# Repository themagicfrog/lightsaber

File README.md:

# MAGIC FROG'S LIGHTSABER

This is a PCB lightsaber controlled by a gyroscope and accelerometer that I designed. I created it originally for [The Trail](https://github.com/hackclub/the-trail), an event organized by [Hack Club](https://github.com/hackclub). 

## Project Overview
I initially designed the entire board with a ATmeag32U4 chip, and you can find the schematic and PCB design in the main branch. I also added some lighthouse-themed silkscreens as my original idea was to make it a desk lamp. I encountered a lot of problems along way and decided to use an Ardunio Nano instead. I used my PCB board as a base and connected the Ardunio Nano. 

## Features
Dynamic LED Control: LEDs light up based on movement detected by the gyroscope and acceleromenter.
- The faster you accelerate, the more LEDs illuminate.
- Each axis (x, y, z) on the gyroscope control a different LED color: red, blue, or green.

## Components
- Ardunio Nano Microcontroller
- MPU-6050 Gyroscope and Accelerometer
- NeoPixel LED Strip
- 6V Battery

## Photos!!
Here are some really cool long-exposure light photos I took with the lightsaber in action!

## Video
[Demo](https://youtu.be/aVmNQV3bQB4)

## Acknowledgements
Special thanks to [Thomas Stubblefield](https://github.com/serenityUX), Kevin Yang, and [Isaac Davenport](https://isaacdavenport.com/) for helping and encouraging me on the way!

## License
Magic Frog's Lightsaber is licensed under the MIT License. See the full license text in [License](https://github.com/themagicfrog/lightsaber/blob/main/LICENSE).

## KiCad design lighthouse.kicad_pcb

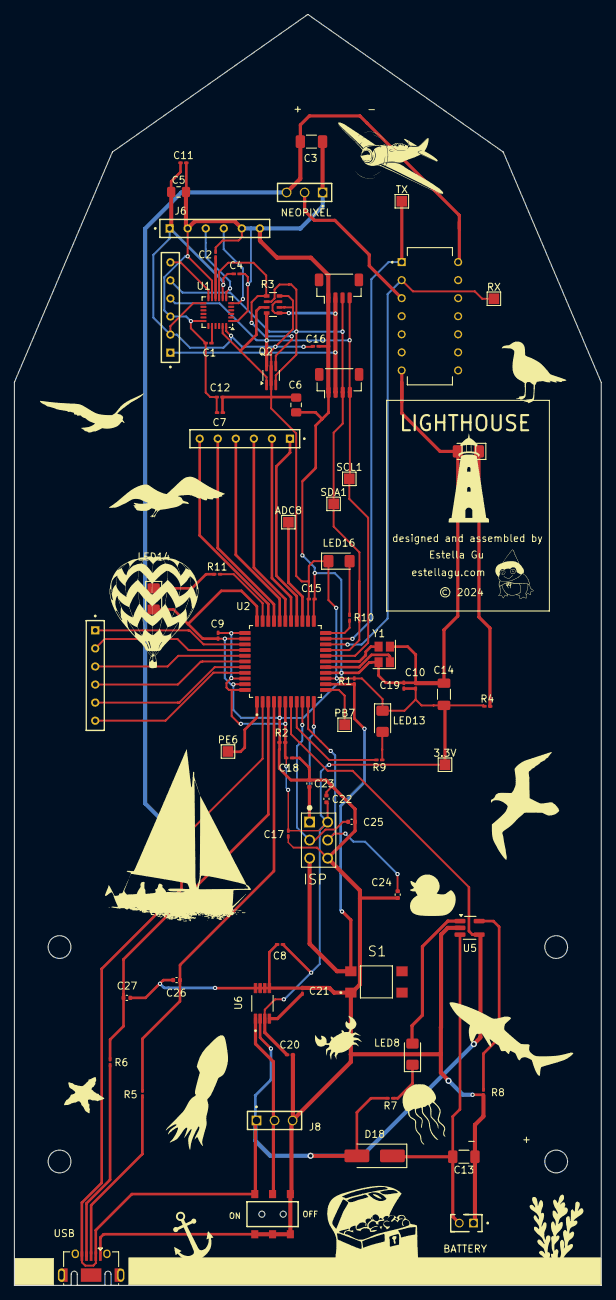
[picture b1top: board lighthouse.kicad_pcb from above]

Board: 2 copper layers, 82.5 x 178.7 mm, 76 parts (0 on the bottom side), 54 nets.

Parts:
3.3V: SEWTAP9; TestPoint_Pad_1.5x1.5mm
ADC8: SEWTAP9; TestPoint_Pad_1.5x1.5mm
BATTERY: MTMM-102-06-L-S-250
C1: 2.2nF; C_0201_0603Metric_Pad0.64x0.40mm_HandSolder
C2, C7, C8: 0.1uF; C_0201_0603Metric_Pad0.64x0.40mm_HandSolder
C3, C13, C14: 4.7uF; C_1206_3216Metric_Pad1.33x1.80mm_HandSolder
C4, C9, C12: .1uF; C_0201_0603Metric_Pad0.64x0.40mm_HandSolder
C5, C6: 10uF; C_0805_2012Metric_Pad1.18x1.45mm_HandSolder
C10, C11, C15, C16, C17, C19, C20: C-EUC0603; C_0201_0603Metric_Pad0.64x0.40mm_HandSolder
C18: 1uF; C_0201_0603Metric_Pad0.64x0.40mm_HandSolder
C21: 470pF; C_0201_0603Metric_Pad0.64x0.40mm_HandSolder
C22: 2.2uF; C_0402_1005Metric
C23, C24, C25, C26, C27: 10pF; C_0402_1005Metric
CONN3, CONN4: STEMMA_I2C_QT; JST_SH_BM04B-SRSS-TB_1x04-1MP_P1.00mm_Vertical
D18: DIODE-SCHOTTKY-B340A; D_SMA_Handsoldering
H1, H2, H3, H4: MountingHole; MountingHole_3.2mm_M3
ISP: 67997-206HLF
J3, J4, J5, J6: BBS-106-X-X
J8: TSW-101-23-L-T
LED1: GREEN; LED_1206_3216Metric_Pad1.42x1.75mm_HandSolder
LED8, LED13, LED14, LED16: RED; LED_1206_3216Metric_Pad1.42x1.75mm_HandSolder
NEOPIXEL: TSW-101-23-L-T
ON: SWITCH-DPDTAYZ0202; AYZ0202
PB7: SEWTAP9; TestPoint_Pad_1.5x1.5mm
PE6: SEWTAP9; TestPoint_Pad_1.5x1.5mm
Q2: BSS138; SOT-363_SC-70-6_Handsoldering
R1, R8: 10k; R_0201_0603Metric_Pad0.64x0.40mm_HandSolder
R2, R4: 10K; R_0201_0603Metric_Pad0.64x0.40mm_HandSolder
R3: 10K; R_Array_Convex_4x0603
R5, R6: 22; R_0201_0603Metric_Pad0.64x0.40mm_HandSolder
R7, R9, R10, R11: 330; R_0201_0603Metric_Pad0.64x0.40mm_HandSolder
RX: SEWTAP9; TestPoint_Pad_1.5x1.5mm
S1: TL3305BF160QG; SW_TL3305BF160QG
SCL1: SEWTAP9; TestPoint_Pad_1.5x1.5mm
SDA1: SEWTAP9; TestPoint_Pad_1.5x1.5mm
TX: SEWTAP9; TestPoint_Pad_1.5x1.5mm
U1: MPU-6050; InvenSense_QFN-24_4x4mm_P0.5mm
U2: ATMEGA32U41:1-LESS_PASTE; ATMEGA32U4-AUR
U5: MCP73831; SOT-23-5_HandSoldering
U6: MIC5219
U7: 74AHCT125; DIP794W45P254L1930H508Q14
USB: USB-ABCONN-11794; USB_Micro-AB_Molex_47590-0001
Y1: Crystal_GND24; Crystal_SMD_SeikoEpson_TSX3225-4Pin_3.2x2.5mm

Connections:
3.3V: 3.3V.1, C4.2, C5.1, C6.1, C7.1, C8.1, C9.2, C10.1, C11.1, C12.2, C14.2, C15.1, C16.1, C17.1, C18.2, C19.1, C20.1, C22.2, ISP.2, J5.02, J6.01, LED13.1 (A), LED16.1 (A), Q2.2 (G), Q2.5 (G), R1.1, R2.1, R3.2 (1), R3.4 (1), R4.1, U1.8 (VLOGIC), U1.13 (VDD), U1.24 (SDA), U2.6 (UCAP), U2.14 (VCC@14), U2.24 (AVCC@24), U2.34 (VCC@34), U2.42 (AREF), U2.44 (AVCC@44), U6.3 (OUT)
5V: C3.2, D18.2 (C), J8.01, NEOPIXEL.03, ON.1, R7.2, U2.2 (UVCC), U2.7 (VBUS), U5.4 (VIN), U6.2 (IN), USB.2 (D-), USB.5 (GND)
/CPOUT: C1.1, U1.20 (CPOUT)
/D+: C26.1, R5.1, U2.4 (D+)
/D-: C27.1, R6.1, U2.3 (D-)
/INT: J5.06, U1.12 (INT)
/REGOUT: C2.1, U1.10 (REGOUT)
/RX_LED: R9.2, U2.8 (PB0(SS))
/SCL: CONN3.4 (SCL), CONN4.4 (SCL), J5.04, Q2.6 (D), R3.8 (2), SCL1.1, U2.18 (PD0(SCL))
/SCL_3V: Q2.1 (S), R3.7 (2), U1.23 (SCL)
/SCL_EXT: J6.03, U1.7 (AUX_CL)
/SDA: CONN3.3 (SDA), CONN4.3 (SDA), J5.05, Q2.3 (D), R3.6 (2), SDA1.1, U2.19 (PD1(SDA))
/SDA_3V: Q2.4 (S), R3.5 (2), U1.9 (AD0)
/SDA_EXT: J6.04, U1.6 (AUX_DA)
/TX_LED: R10.2, U2.22 (PD5)
/USER_LED: R11.2, U2.32 (PC7)
GND: BATTERY.01, C1.2, C2.2, C3.1, C4.1, C5.2, C6.2, C7.2, C8.2, C9.1, C10.2, C11.2, C12.1, C13.1, C14.1, C15.2, C16.2, C17.2, C18.1, C19.2, C20.2, C21.1, C22.1, C23.2, C24.2, C25.1, C26.2, C27.2, CONN3.1 (GND), CONN4.1 (GND), ISP.6, J5.03, J6.02, J6.05, J6.06, J8.03, LED1.2 (C), LED14.2 (C), NEOPIXEL.01, ON.3, ON.4, ON.5, ON.6, R2.2, R8.1, S1.1, U1.1 (CLKIN), U1.11 (FSYNC), U1.18 (GND), U2.5 (UGND), U2.15 (GND@15), U2.23 (GND@23), U2.33 (PE2/~HWB), U2.35 (GND@35), U2.43 (GND@43), U5.2 (VSS), U6.5 (GND), U6.6 (GND), U6.7 (GND), U6.8 (GND), USB.1 (VBUS), Y1.2, Y1.4
unnamed: LED1.1 (A), R4.2
unnamed: LED8.1 (A), R7.1
unnamed: LED8.2 (C), U5.1 (STAT)
unnamed: LED13.2 (C), R9.1
unnamed: LED14.1 (A), R11.1
unnamed: LED16.2 (C), R10.1
unnamed: NEOPIXEL.02, U7.3
unnamed: ISP.5, R1.2, S1.3 (2), U2.13 (~RESET)
unnamed: C25.2, ISP.3, U2.9 (PB1(SCK))
unnamed: C24.1, ISP.4, U2.10 (PB2(MOSI))
unnamed: C23.1, ISP.1, U2.11 (PB3(MISO))
unnamed: J4.03, U2.28 (PB4(ADC11))
unnamed: J4.04, U2.29 (PB5(ADC12))
unnamed: J4.05, U2.30 (PB6(ADC13))
unnamed: PB7.1, U2.12 (PB7)
unnamed: J4.06, U2.31 (PC6)
unnamed: RX.1, U2.20 (PD2(RX)), U7.2
unnamed: TX.1, U2.21 (PD3(TX)), U7.1
unnamed: ADC8.1, U2.25 (PD4(ADC8))
unnamed: J4.01, U2.26 (PD6(ADC9))
unnamed: J4.02, U2.27 (PD7(ADC10))
unnamed: PE6.1, U2.1 (PE6)
unnamed: J3.06, U2.41 (PF0(ADC0))
unnamed: J3.05, U2.40 (PF1(ADC1))
unnamed: J3.04, U2.39 (PF4(ADC4))
unnamed: J3.03, U2.38 (PF5(ADC5))
unnamed: J3.02, U2.37 (PF6(ADC6))
unnamed: J3.01, U2.36 (PF7(ADC7))
unnamed: U2.17 (XTAL1), Y1.3
unnamed: U2.16 (XTAL2), Y1.1
unnamed: R8.2, U5.5 (PROG)
unnamed: C21.2, U6.4 (BYP)
unnamed: J8.02, ON.2, U6.1 (EN)
unnamed: R5.2, USB.3 (D+)
unnamed: R6.2, USB.4 (USBID)
VCC: CONN3.2 (V+), CONN4.2 (V+), J5.01, R3.1, R3.3 (1)
V_BATT: BATTERY.02, C13.2, D18.1 (A), U5.3 (VBAT)

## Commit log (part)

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2024-08-23 Rename lightsaber1.JPG to demophoto1.JPG
2024-08-23 Rename lightsaber2.JPG to demophoto2.JPG
2024-08-23 Rename lightsaber3.JPG to demophoto3.JPG
2024-08-23 Rename lightsaber4.JPG to demophoto4.JPG
2024-08-23 Rename lightsaber5.JPG to demophoto5.JPG
2024-08-23 Rename lightsaber6.JPG to pcbphoto1.JPG
2024-08-23 Rename lightsaber7.JPG to pcbphoto2.JPG
2024-08-23 Rename lightsaber8.JPG to pcbphoto3.JPG
2024-08-23 Add ardunio code
2024-08-23 Add pcb schematic
2024-08-23 Add pcb design
2024-08-23 Add all design-related files
2024-08-23 Create demophotos
2024-08-23 Create space
2024-08-23 Rename demophoto1.JPG to demophotos/demophoto1.JPG
2024-08-23 Rename demophoto2.JPG to demophotos/demophoto2.JPG
2024-08-23 Rename demophoto3.JPG to demophotos/demophoto3.JPG
2024-08-23 Rename demophoto4.JPG to demophotos/demophoto4.JPG
2024-08-23 Rename demophoto5.JPG to demophotos/demophoto5.JPG
2024-08-23 Rename pcbphoto1.JPG to pcbphotos/pcbphoto1.JPG
2024-08-23 Rename pcbphoto2.JPG to pcbphotos/pcbphoto2.JPG
2024-08-23 Create LICENSE
2024-08-23 Rename demophoto3.JPG to demophoto/demophoto3.JPG

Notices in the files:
lighthouse.kicad_pcb:
© 2024
